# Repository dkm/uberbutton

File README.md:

# uberbutton

Uses RIOT OS : https://github.com/RIOT-OS/RIOT

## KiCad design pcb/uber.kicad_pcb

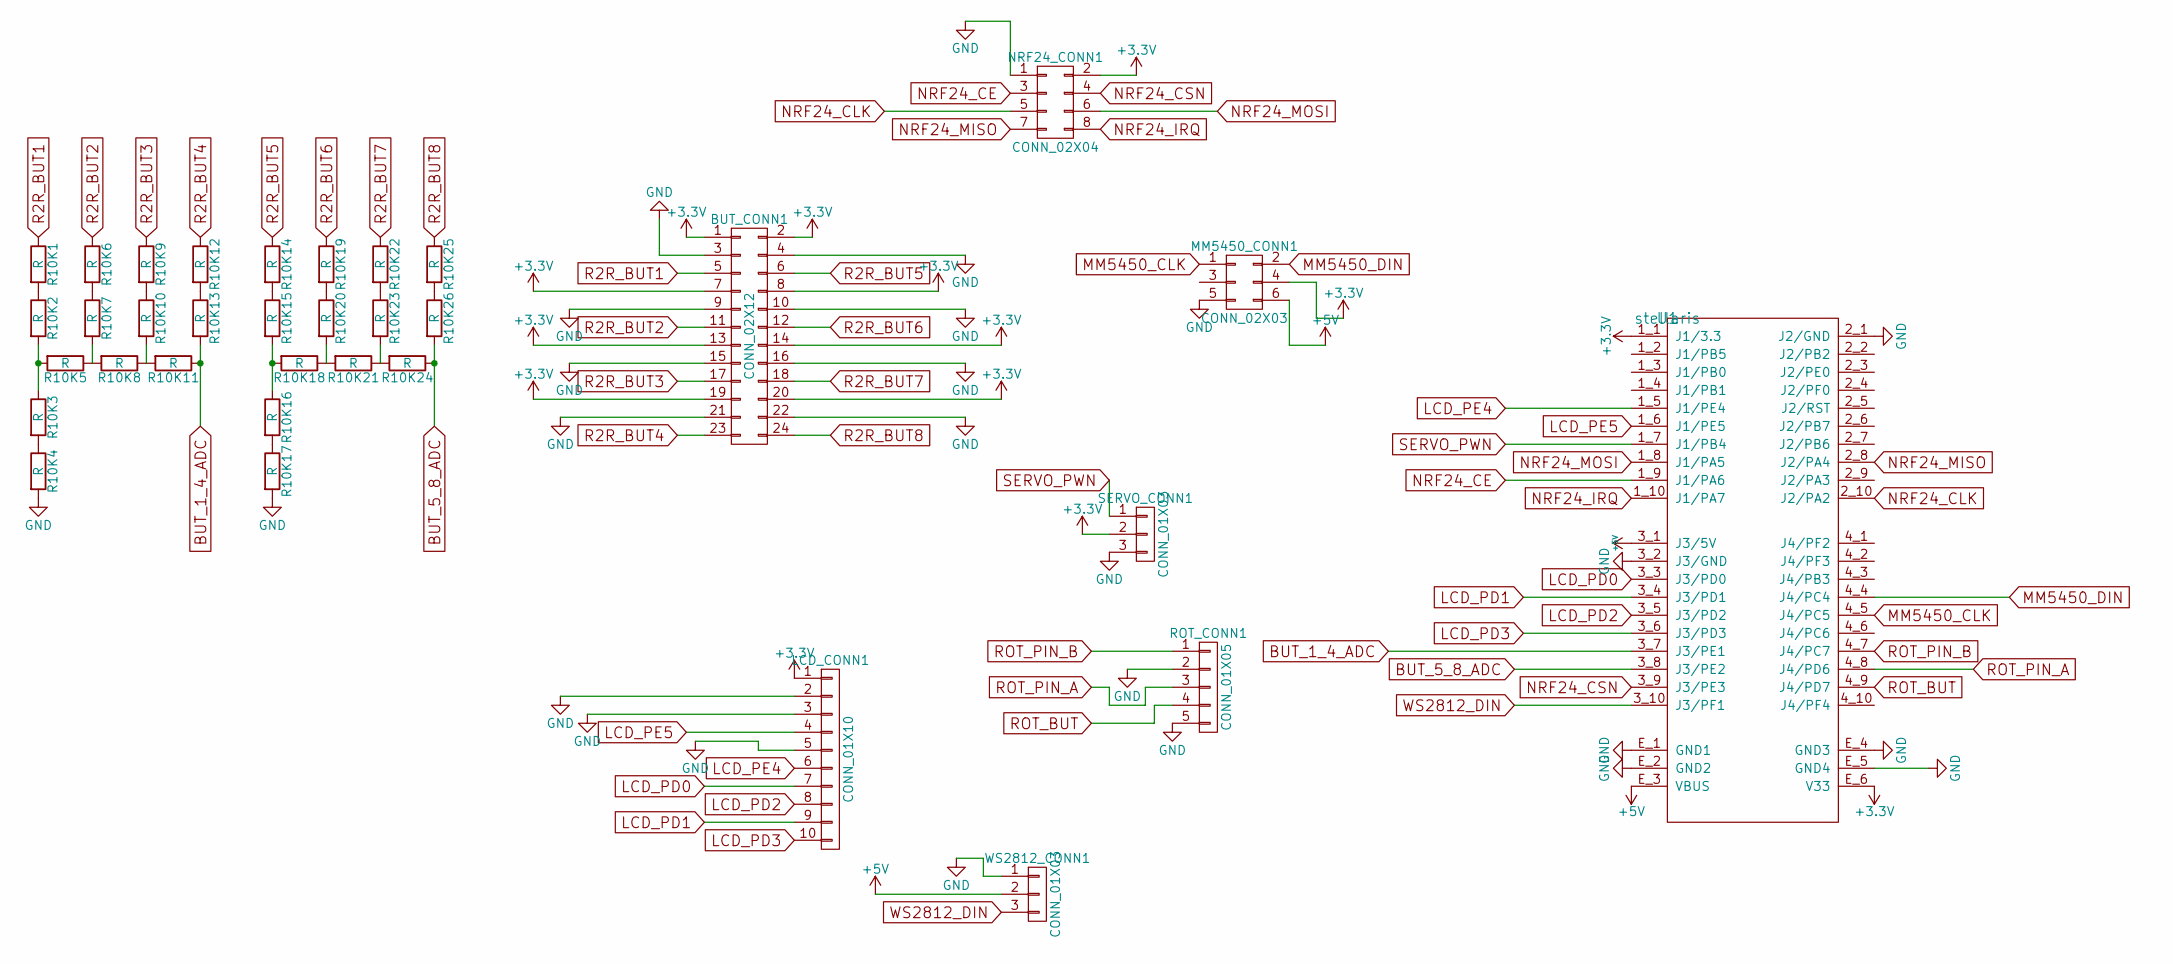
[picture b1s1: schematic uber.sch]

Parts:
BUT_CONN1: CONN_02X12; Pin_Header_Straight_2x12
LCD_CONN1: CONN_01X10; Pin_Header_Straight_1x10
MM5450_CONN1: CONN_02X03; Pin_Header_Straight_1x06
NRF24_CONN1: CONN_02X04; Pin_Header_Straight_2x04
R10K1, R10K2, R10K3, R10K4, R10K5, R10K6, R10K7, R10K8, R10K9, R10K10, R10K11, R10K12, R10K13, R10K14, R10K15, R10K16, R10K17, R10K18, R10K19, R10K20, R10K21, R10K22, R10K23, R10K24, R10K25, R10K26: R; Resistor_Horizontal_RM10mm
ROT_CONN1: CONN_01X05; Pin_Header_Straight_1x05
SERVO_CONN1: CONN_01X03; Pin_Header_Straight_1x03
U1: stellaris; stellaris_launchpad
WS2812_CONN1: CONN_01X03; Pin_Header_Straight_1x03

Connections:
+3V3: BUT_CONN1.1, BUT_CONN1.2, BUT_CONN1.7, BUT_CONN1.8, BUT_CONN1.13, BUT_CONN1.14, BUT_CONN1.19, BUT_CONN1.20, LCD_CONN1.1, MM5450_CONN1.4, NRF24_CONN1.2, SERVO_CONN1.2, U1.1_1 (J1/3.3), U1.E_6 (V33)
+5V: MM5450_CONN1.6, U1.3_1 (J3/5V), U1.E_3 (VBUS), WS2812_CONN1.2
BUT_1_4_ADC: R10K11.1, R10K13.2, U1.3_7 (J3/PE1)
BUT_5_8_ADC: R10K24.1, R10K26.2, U1.3_8 (J3/PE2)
GND: BUT_CONN1.3, BUT_CONN1.4, BUT_CONN1.9, BUT_CONN1.10, BUT_CONN1.15, BUT_CONN1.16, BUT_CONN1.21, BUT_CONN1.22, LCD_CONN1.2, LCD_CONN1.3, LCD_CONN1.5, MM5450_CONN1.5, NRF24_CONN1.1, R10K4.2, R10K17.2, ROT_CONN1.2, ROT_CONN1.5, SERVO_CONN1.3, U1.2_1 (J2/GND), U1.3_2 (J3/GND), U1.E_1 (GND1), U1.E_2 (GND2), U1.E_4 (GND3), U1.E_5 (GND4), WS2812_CONN1.1
LCD_PD0: LCD_CONN1.7, U1.3_3 (J3/PD0)
LCD_PD1: LCD_CONN1.9, U1.3_4 (J3/PD1)
LCD_PD2: LCD_CONN1.8, U1.3_5 (J3/PD2)
LCD_PD3: LCD_CONN1.10, U1.3_6 (J3/PD3)
LCD_PE4: LCD_CONN1.6, U1.1_5 (J1/PE4)
LCD_PE5: LCD_CONN1.4, U1.1_6 (J1/PE5)
MM5450_CLK: MM5450_CONN1.1, U1.4_5 (J4/PC5)
MM5450_DIN: MM5450_CONN1.2, U1.4_4 (J4/PC4)
NRF24_CE: NRF24_CONN1.3, U1.1_9 (J1/PA6)
NRF24_CLK: NRF24_CONN1.5, U1.2_10 (J2/PA2)
NRF24_CSN: NRF24_CONN1.4, U1.3_9 (J3/PE3)
NRF24_IRQ: NRF24_CONN1.8, U1.1_10 (J1/PA7)
NRF24_MISO: NRF24_CONN1.7, U1.2_8 (J2/PA4)
NRF24_MOSI: NRF24_CONN1.6, U1.1_8 (J1/PA5)
unnamed: R10K1.2, R10K2.1
unnamed: R10K2.2, R10K3.1, R10K5.2
unnamed: R10K3.2, R10K4.1
unnamed: R10K5.1, R10K7.2, R10K8.2
unnamed: R10K6.2, R10K7.1
unnamed: R10K9.2, R10K10.1
unnamed: R10K8.1, R10K10.2, R10K11.2
unnamed: R10K12.2, R10K13.1
unnamed: R10K14.2, R10K15.1
unnamed: R10K15.2, R10K16.1, R10K18.2
unnamed: R10K16.2, R10K17.1
unnamed: R10K18.1, R10K20.2, R10K21.2
unnamed: R10K19.2, R10K20.1
unnamed: R10K21.1, R10K23.2, R10K24.2
unnamed: R10K22.2, R10K23.1
unnamed: R10K25.2, R10K26.1
R2R_BUT1: BUT_CONN1.5, R10K1.1
R2R_BUT2: BUT_CONN1.11, R10K6.1
R2R_BUT3: BUT_CONN1.17, R10K9.1
R2R_BUT4: BUT_CONN1.23, R10K12.1
R2R_BUT5: BUT_CONN1.6, R10K14.1
R2R_BUT6: BUT_CONN1.12, R10K19.1
R2R_BUT7: BUT_CONN1.18, R10K22.1
R2R_BUT8: BUT_CONN1.24, R10K25.1
ROT_BUT: ROT_CONN1.4, U1.4_9 (J4/PD7)
ROT_PIN_A: ROT_CONN1.3, U1.4_8 (J4/PD6)
ROT_PIN_B: ROT_CONN1.1, U1.4_7 (J4/PC7)
SERVO_PWN: SERVO_CONN1.1, U1.1_7 (J1/PB4)
WS2812_DIN: U1.3_10 (J3/PF1), WS2812_CONN1.3

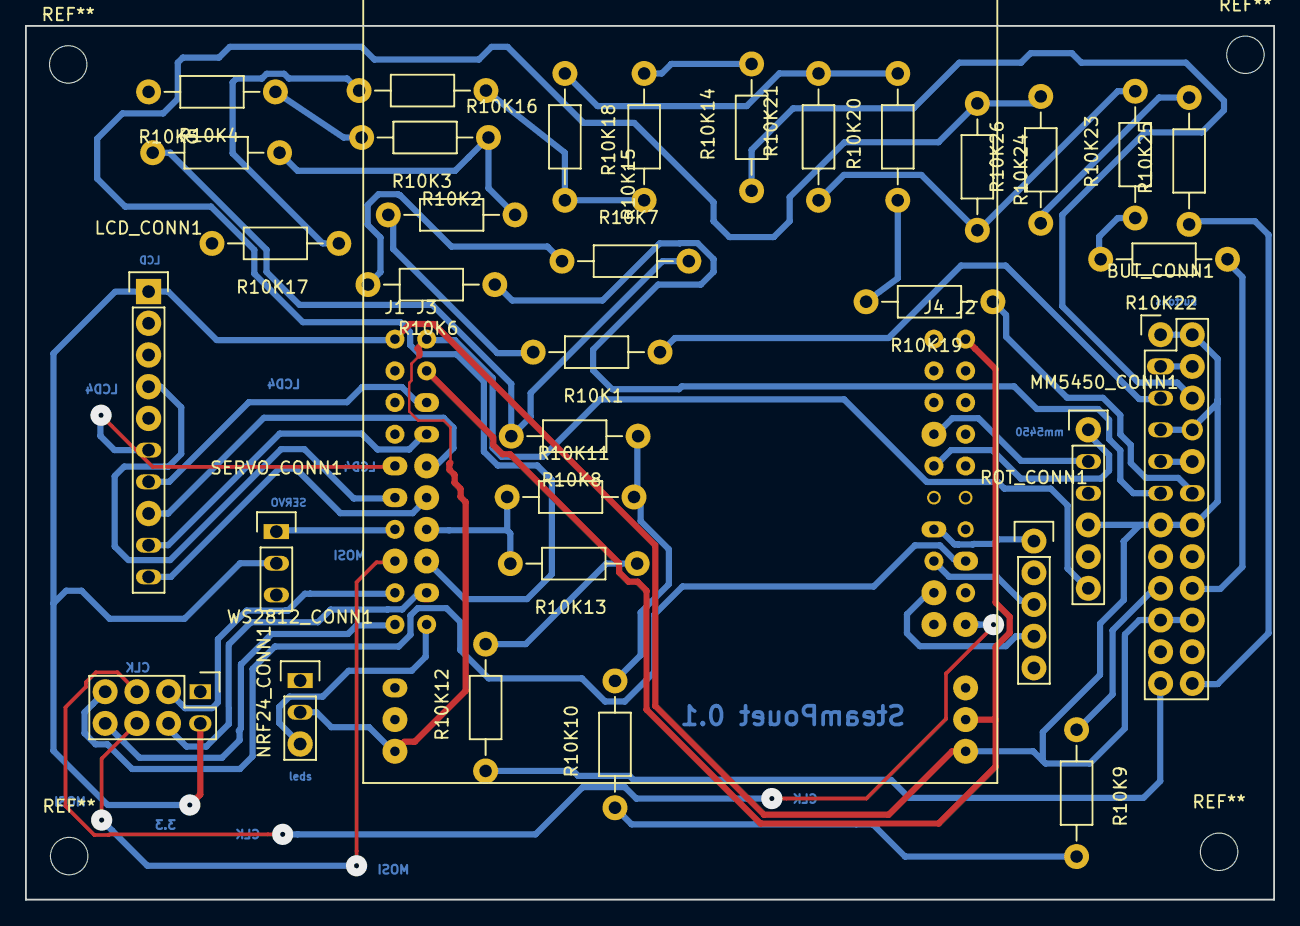
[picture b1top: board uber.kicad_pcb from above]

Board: 2 copper layers, 100.0 x 70.0 mm, 34 parts (0 on the bottom side), 48 nets.

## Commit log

2016-01-13 first import, working with nrf
2016-01-26 just works, before ws2812
2016-02-26 ugly dump of working (kind of) code
2016-03-23 before rotary code
2016-04-05 Use rotary module in RIOT
2016-05-11 Clean conditional compilation + rebase
    - use if instead of ifdef
    - rebase on top of latest upstream RIOT
2016-05-12 use uDMA for drivings leds
    WIP. It is working, but needs some love(tm)
2016-05-20 fix ws2812
2016-05-20 fix dma rate
2016-05-20 rainbow power
2016-06-07 first version of PCB
2016-06-07 reworked the ground plane
    kicad still reports unconnected pads. After having triple-checked by hand, all GND pads are connected to one of the 2 GND.
2016-06-08 fix stellaris board pin distance.
2016-06-09 correct stellaris headers spacing.... library one was not correct
2016-06-09 even finer spacing fix
2016-06-14 stellaris board footprint + component update PCB
2016-06-14 add some fancy name on the board
2016-06-15 add mounting holes and more labels on board
2016-06-15 enl4rg3 some p4ds
2016-06-15 make the ground plane a bit more robust to DIY print with largest tracks
2016-08-09 Clean servo handling and use for notif
2016-08-09 Better led notif on event
2016-08-09 some more work for lcd display
    still some queue ovrfl and probably some timing issue with LCD when IT
    are raised (eg. when using rotary)
2017-07-10 Create README.md
    Make RIOT dep explicit
